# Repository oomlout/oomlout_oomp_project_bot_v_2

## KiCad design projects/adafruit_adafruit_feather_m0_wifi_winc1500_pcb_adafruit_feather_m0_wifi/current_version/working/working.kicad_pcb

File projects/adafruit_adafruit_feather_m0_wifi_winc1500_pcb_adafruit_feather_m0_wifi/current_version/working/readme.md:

# adafruit_feather_m0_wifi_winc1500_pcb
 
## summary 
* id: adafruit_adafruit_feather_m0_wifi_winc1500_pcb_adafruit_feather_m0_wifi
* user: adafruit
* name: adafruit_feather_m0_wifi_winc1500_pcb
* board: adafruit_feather_m0_wifi
* repo: https://github.com/adafruit/Adafruit-Feather-M0-WiFi-WINC1500-PCB

* src_file_repo_sch: 
* src_file_repo_sch_link: https://github.com/adafruit/Adafruit-Feather-M0-WiFi-WINC1500-PCB/tree/master/
* full details link: https://github.com/oomlout/oomlout_oomp_project_bot_v_2/tree/main/projects/adafruit_adafruit_feather_m0_wifi_winc1500_pcb_adafruit_feather_m0_wifi/current_version/working  

## schematic  
  
[schematic (pdf)](working_schematic.pdf) 

## pcb  

[board (pdf)](working.pdf)  

## working_bom
| Id | Designator | Footprint | Quantity | Designation | Supplier and ref |  | None | 
| --- | --- | --- | --- | --- | --- | --- | --- | 
| 1 | X1 | JSTPH2 | 1 | JSTPH |  |  | [''] | 
| 2 | R2,R11 | 0603-NO | 2 | 1K |  |  | [''] | 
| 3 | R10,R5 | 0603-NO | 2 | 1k |  |  | [''] | 
| 4 | R6 | 0603-NO | 1 | 100K |  |  | [''] | 
| 5 | U$32,U$31 | MOUNTINGHOLE_2.5_PLATED | 2 | MOUNTINGHOLE2.5 |  |  | [''] | 
| 6 | @HOLE1,@HOLE0 |  | 2 |  |  |  | [''] | 
| 7 | R3,R9,R1,R4 | 0603-NO | 4 | 100k |  |  | [''] | 
| 8 | NET0 | CHIPLED_0805_NOOUTLINE | 1 | YELLOW |  |  | [''] | 
| 9 | C2,C4 | 0603-NO | 2 | 22pF |  |  | [''] | 
| 10 | X3 | 4UCONN_20329_V2 | 1 | microUSB |  |  | [''] | 
| 11 | C14,C7,C1 | 0603-NO | 3 | 1uF |  |  | [''] | 
| 12 | U$7,U$12 | ADAFRUIT_3.5MM | 2 |  |  |  | [''] | 
| 13 | C8,C3,C6 | 0805-NO | 3 | 10ÂµF |  |  | [''] | 
| 14 | U$35,U$34 | FIDUCIAL_1MM | 2 | FIDUCIAL" |  |  | [''] | 
| 15 | U2 | SOT23-5 | 1 | AP2112K-3.3 |  |  | [''] | 
| 16 | JP1 | 1X16_ROUND | 1 |  |  |  | [''] | 
| 17 | WIFI0 | CHIPLED_0805_NOOUTLINE | 1 | GREEN |  |  | [''] | 
| 18 | C5 | 0805-NO | 1 | 10uF |  |  | [''] | 
| 19 | U3 | SOT23-5 | 1 | MCP73831T-2ACI/OT |  |  | [''] | 
| 20 | L0 | CHIPLED_0805_NOOUTLINE | 1 | RED |  |  | [''] | 
| 21 | X2 | XTAL3215 | 1 | 32.768 |  |  | [''] | 
| 22 | CHG0 | CHIPLED_0805_NOOUTLINE | 1 | ORANGE |  |  | [''] | 
| 23 | X4 | ATWINC1500_MR210PA | 1 | ATWINC1500_MR210PA |  |  | [''] | 
| 24 | R7 | 0603-NO | 1 | 2.2K |  |  | [''] | 
| 25 | U$4 | TQFN48_7MM | 1 | ATSAMD21G18_QFN |  |  | [''] | 
| 26 | D1 | SOD-123 | 1 | MBR120 |  |  | [''] | 
| 27 | JP3 | 1X12_ROUND | 1 |  |  |  | [''] | 
| 28 | SW1 | KMR2 | 1 | SPST_TACT-KMR2 |  |  | [''] | 
| 29 | R8 | 0603-NO | 1 | 4.7K |  |  | [''] | 
| 30 | TP1,TP2 | TESTPOINT_ROUND_1.5MM | 2 |  |  |  | [''] | 
| 31 | U$9 | FEATHERLOGO | 1 |  |  |  | [''] | 
| 32 | U$13 | PCBFEAT-REV-040 | 1 |  |  |  | [''] | 

## bom_schematic
| Ref | Qnty | Value | Cmp name | Footprint | Description | Vendor | DNP | 
| --- | --- | --- | --- | --- | --- | --- | --- | 
| C1, C7, C14 | 3 | 1uF | CAP_CERAMIC0603_NO | working:0603-NO |  |  |  | 
| C2, C4 | 2 | 22pF | CAP_CERAMIC0603_NO | working:0603-NO |  |  |  | 
| C3, C6, C8 | 3 | 10ÂµF | CAP_CERAMIC0805-NOOUTLINE | working:0805-NO |  |  |  | 
| C5 | 1 | 10uF | CAP_CERAMIC0805-NOOUTLINE | working:0805-NO |  |  |  | 
| CHG0 | 1 | ORANGE | LED0805_NOOUTLINE | working:CHIPLED_0805_NOOUTLINE |  |  |  | 
| D1 | 1 | MBR120 | DIODE-SCHOTTKYSOD-123 | working:SOD-123 |  |  |  | 
| JP1 | 1 | HEADER-1X16ROUND | HEADER-1X16ROUND | working:1X16_ROUND |  |  |  | 
| JP3 | 1 | HEADER-1X12 | HEADER-1X12 | working:1X12_ROUND |  |  |  | 
| L0 | 1 | RED | LED0805_NOOUTLINE | working:CHIPLED_0805_NOOUTLINE |  |  |  | 
| NET0 | 1 | YELLOW | LED0805_NOOUTLINE | working:CHIPLED_0805_NOOUTLINE |  |  |  | 
| R1, R3, R4, R9 | 4 | 100k | RESISTOR_0603_NOOUT | working:0603-NO |  |  |  | 
| R2, R11 | 2 | 1K | RESISTOR_0603_NOOUT | working:0603-NO |  |  |  | 
| R5, R10 | 2 | 1k | RESISTOR_0603_NOOUT | working:0603-NO |  |  |  | 
| R6 | 1 | 100K | RESISTOR_0603_NOOUT | working:0603-NO |  |  |  | 
| R7 | 1 | 2.2K | RESISTOR_0603_NOOUT | working:0603-NO |  |  |  | 
| R8 | 1 | 4.7K | RESISTOR_0603_NOOUT | working:0603-NO |  |  |  | 
| SW1 | 1 | SPST_TACT-KMR2 | SPST_TACT-KMR2 | working:KMR2 |  |  |  | 
| TP1, TP2 | 2 | TESTPOINTROUND1.5MM | TESTPOINTROUND1.5MM | working:TESTPOINT_ROUND_1.5MM |  |  |  | 
| U2 | 1 | AP2112K-3.3 | VREG_SOT23-5 | working:SOT23-5 |  |  |  | 
| U3 | 1 | MCP73831T-2ACI/OT | MCP73831/2 | working:SOT23-5 |  |  |  | 
| U$4 | 1 | ATSAMD21J_QFN | ATSAMD21J_QFN | working:TQFN48_7MM |  |  |  | 
| U$31, U$32 | 2 | MOUNTINGHOLE2.5 | MOUNTINGHOLE2.5 | working:MOUNTINGHOLE_2.5_PLATED |  |  |  | 
| U$34, U$35 | 2 | FIDUCIAL"" | FIDUCIAL{dblquote}{dblquote} | working:FIDUCIAL_1MM |  |  |  | 
| WIFI0 | 1 | GREEN | LED0805_NOOUTLINE | working:CHIPLED_0805_NOOUTLINE |  |  |  | 
| X1 | 1 | JSTPH | CON_JST_PH_2PIN | working:JSTPH2 |  |  |  | 
| X2 | 1 | 32.768 | XTAL-3.2X1.5 | working:XTAL3215 |  |  |  | 
| X3 | 1 | microUSB | USB_MICRO_20329_V2 | working:4UCONN_20329_V2 |  |  |  | 
| X4 | 1 | ATWINC1500_MR210PA | ATWINC1500_MR210PA | working:ATWINC1500_MR210PA |  |  |  | 

## mounting_holes
| x | y | package | value | ref | size | 
| --- | --- | --- | --- | --- | --- | 
| 0.0 | 17.78 | MOUNTINGHOLE_2.5_PLATED | MOUNTINGHOLE2.5 | U$31 | m3 | 
| 0.0 | 0.0 | MOUNTINGHOLE_2.5_PLATED | MOUNTINGHOLE2.5 | U$32 | m3 |

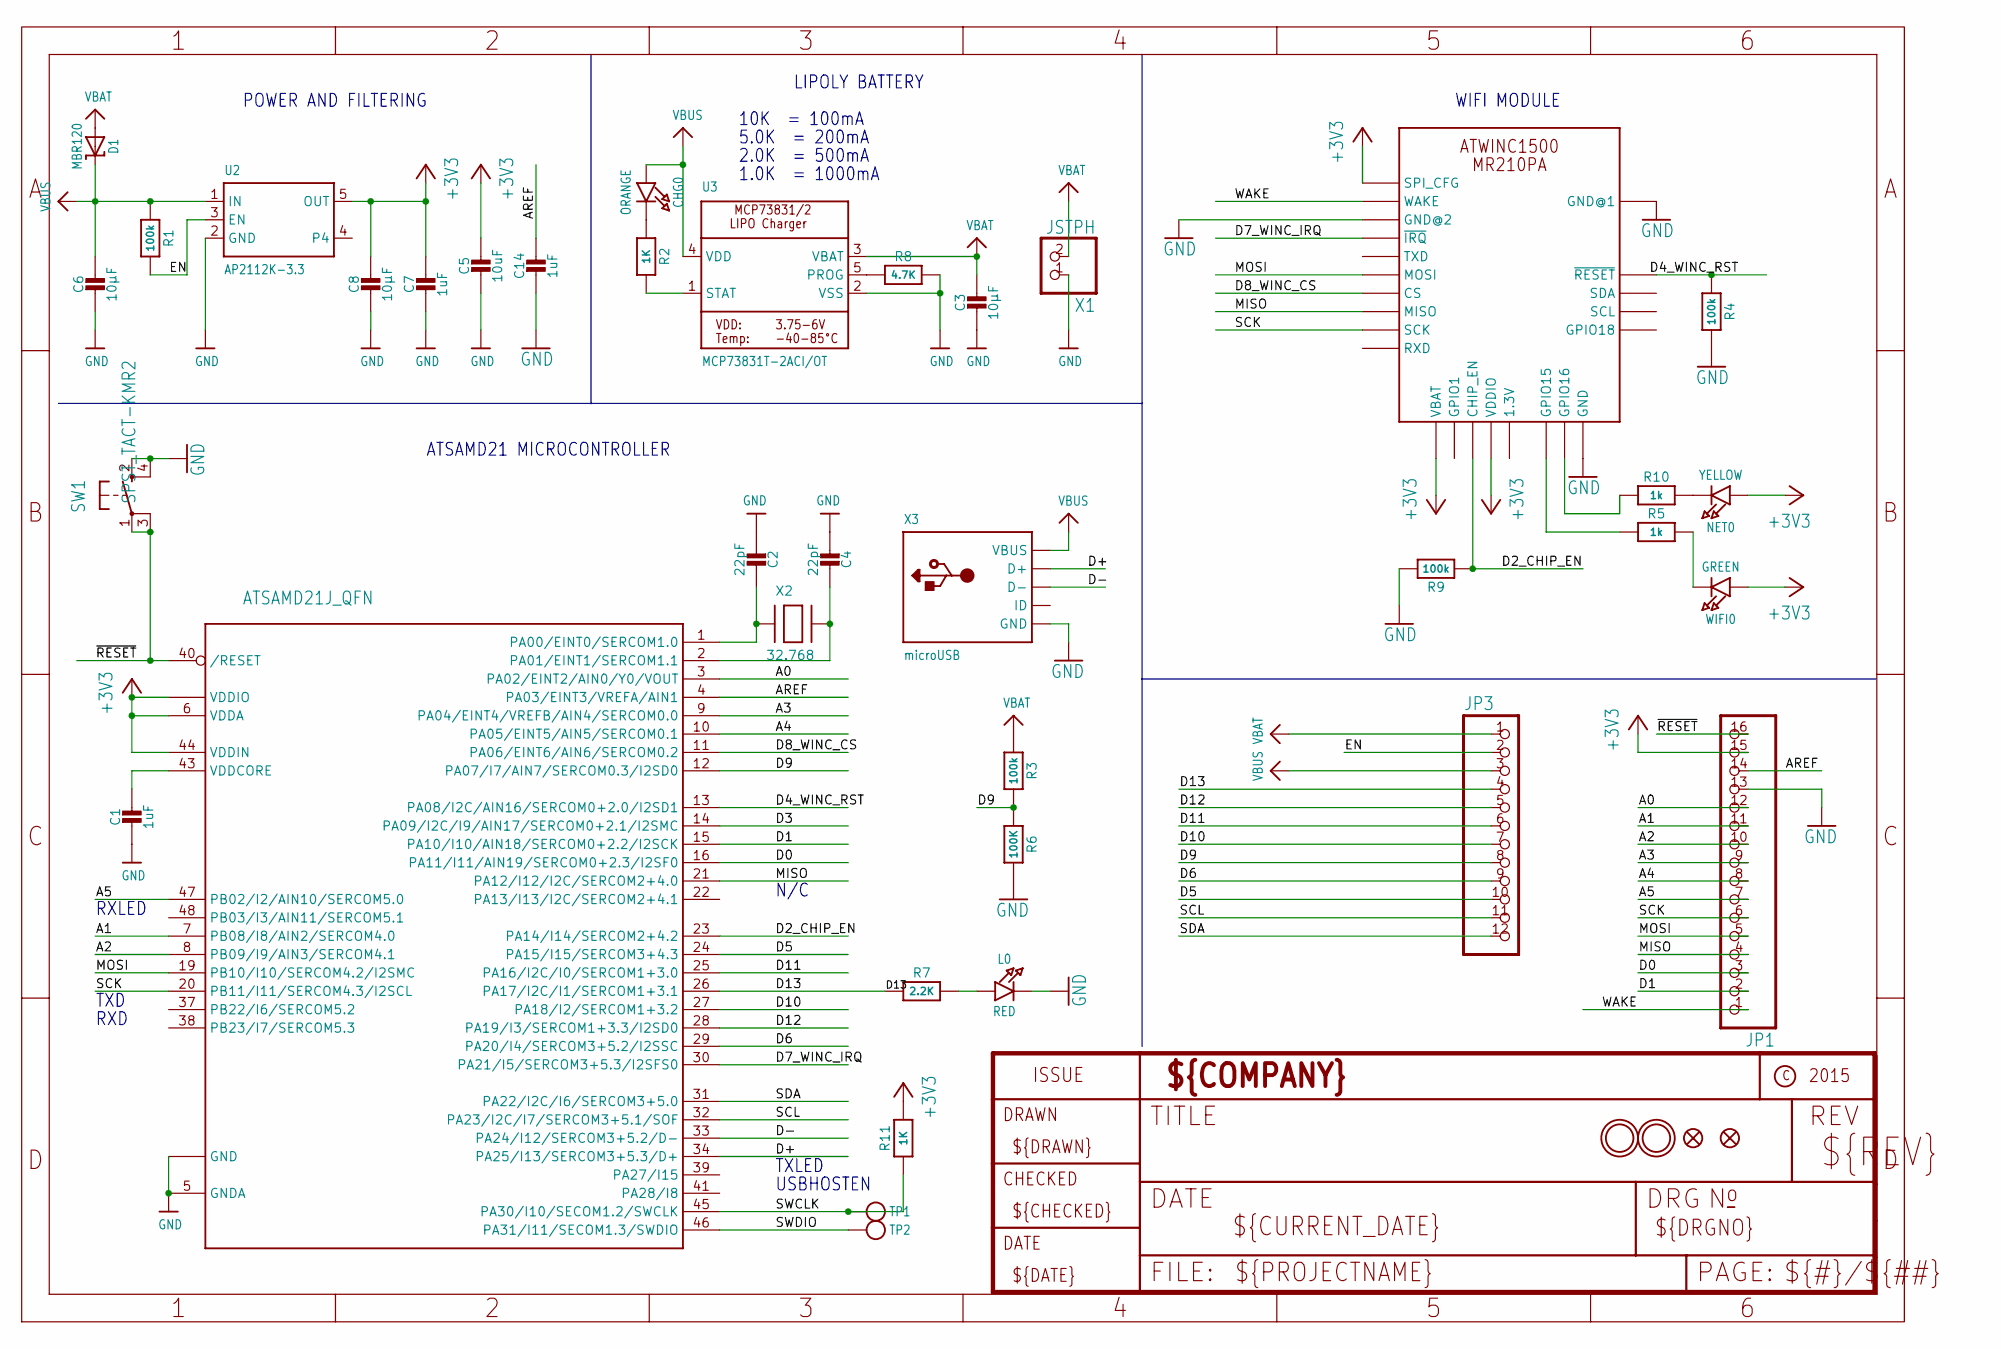
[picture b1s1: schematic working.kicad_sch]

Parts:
C1, C7, C14: 1uF; 0603-NO
C2, C4: 22pF; 0603-NO
C3, C6, C8: 10µF; 0805-NO
C5: 10uF; 0805-NO
CHG0: ORANGE; CHIPLED_0805_NOOUTLINE
D1: MBR120; SOD-123
JP1: HEADER-1X16ROUND; 1X16_ROUND
JP3: HEADER-1X12; 1X12_ROUND
L0: RED; CHIPLED_0805_NOOUTLINE
NET0: YELLOW; CHIPLED_0805_NOOUTLINE
R1, R3, R4, R9: 100k; 0603-NO
R2, R11: 1K; 0603-NO
R5, R10: 1k; 0603-NO
R6: 100K; 0603-NO
R7: 2.2K; 0603-NO
R8: 4.7K; 0603-NO
SW1: SPST_TACT-KMR2; KMR2
TP1, TP2: TESTPOINTROUND1.5MM; TESTPOINT_ROUND_1.5MM
U2: AP2112K-3.3; SOT23-5
U3: MCP73831T-2ACI/OT; SOT23-5
U$4: ATSAMD21J_QFN; TQFN48_7MM
U$31, U$32: MOUNTINGHOLE2.5; MOUNTINGHOLE_2.5_PLATED
U$34, U$35: FIDUCIAL""; FIDUCIAL_1MM
WIFI0: GREEN; CHIPLED_0805_NOOUTLINE
X1: JSTPH; JSTPH2
X2: 32.768; XTAL3215
X3: microUSB; 4UCONN_20329_V2
X4: ATWINC1500_MR210PA

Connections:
+3V3: C5.1, C7.1, C8.1, JP1.15, NET0.A, R11.2, U2.5 (OUT), U$4.6 (VDDA), U$4.17 (VDDIO), U$4.36 (VDDIO), U$4.44 (VDDIN), WIFI0.A, X4.J10 (SPI_CFG), X4.J20 (VBAT), X4.J23 (VDDIO)
A0: JP1.12, U$4.3 (PA02/EINT2/AIN0/Y0/VOUT)
A1: JP1.11, U$4.7 (PB08/I8/AIN2/SERCOM4.0)
A2: JP1.10, U$4.8 (PB09/I9/AIN3/SERCOM4.1)
A3: JP1.9, U$4.9 (PA04/EINT4/VREFB/AIN4/SERCOM0.0)
A4: JP1.8, U$4.10 (PA05/EINT5/AIN5/SERCOM0.1)
A5: JP1.7, U$4.47 (PB02/I2/AIN10/SERCOM5.0)
AREF: C14.1, JP1.14, U$4.4 (PA03/EINT3/VREFA/AIN1)
D0: JP1.3, U$4.16 (PA11/I11/AIN19/SERCOM0+2.3/I2SF0)
D1: JP1.2, U$4.15 (PA10/I10/AIN18/SERCOM0+2.2/I2SCK)
D2_CHIP_EN: R9.1, U$4.23 (PA14/I14/SERCOM2+4.2), X4.J22 (CHIP_EN)
D3: U$4.14 (PA09/I2C/I9/AIN17/SERCOM0+2.1/I2SMC)
D4_WINC_RST: R4.1, U$4.13 (PA08/I2C/AIN16/SERCOM0+2.0/I2SD1), X4.J4 (~RESET)
D5: JP3.10, U$4.24 (PA15/I15/SERCOM3+4.3)
D6: JP3.9, U$4.29 (PA20/I4/SERCOM3+5.2/I2SSC)
D7_WINC_IRQ: U$4.30 (PA21/I5/SERCOM3+5.3/I2SFS0), X4.J13 (~IRQ)
D8_WINC_CS: U$4.11 (PA06/EINT6/AIN6/SERCOM0.2), X4.J16 (CS)
D9: JP3.8, R3.2, R6.1, U$4.12 (PA07/I7/AIN7/SERCOM0.3/I2SD0)
D10: JP3.7, U$4.27 (PA18/I2/SERCOM1+3.2)
D11: JP3.6, U$4.25 (PA16/I2C/I0/SERCOM1+3.0)
D12: JP3.5, U$4.28 (PA19/I3/SERCOM1+3.3/I2SD0)
D13: JP3.4, R7.1, U$4.26 (PA17/I2C/I1/SERCOM1+3.1)
D+: U$4.34 (PA25/I13/SERCOM3+5.3/D+), X3.D+
D-: U$4.33 (PA24/I12/SERCOM3+5.2/D-), X3.D-
EN: JP3.2, R1.2, U2.3 (EN)
GND: C1.2, C2.2, C3.2, C4.2, C5.2, C6.2, C7.2, C8.2, C14.2, JP1.13, L0.C, R4.2, R6.2, R8.2, R9.2, SW1.2 (S), SW1.4 (S1), U2.2 (GND), U3.2 (VSS), U$4.5 (GNDA), U$4.18 (GND), U$4.35 (GND), U$4.42 (GND), U$4.THERMAL (GND), X1.1, X3.BASE@1 (GND), X3.BASE@2 (GND), X3.GND, X3.SPRT@1 (GND), X3.SPRT@2 (GND), X3.SPRT@3 (GND), X3.SPRT@4 (GND), X4.J9 (GND@1), X4.J12 (GND@2), X4.J28 (GND), X4.MTGND (GND)
MISO: JP1.4, U$4.21 (PA12/I12/I2C/SERCOM2+4.0), X4.J17 (MISO)
MOSI: JP1.5, U$4.19 (PB10/I10/SERCOM4.2/I2SMC), X4.J15 (MOSI)
unnamed: CHG0.C, R2.1
unnamed: L0.A, R7.2
unnamed: R2.2, U3.1 (STAT)
unnamed: R8.1, U3.5 (PROG)
unnamed: C2.1, U$4.1 (PA00/EINT0/SERCOM1.0), X2.P$1
unnamed: R5.1, X4.J26 (GPIO15)
unnamed: C4.1, U$4.2 (PA01/EINT1/SERCOM1.1), X2.P$2
unnamed: R10.1, X4.J27 (GPIO16)
unnamed: R5.2, WIFI0.C
unnamed: NET0.C, R10.2
SCK: JP1.6, U$4.20 (PB11/I11/SERCOM4.3/I2SCL), X4.J18 (SCK)
SCL: JP3.11, U$4.32 (PA23/I2C/I7/SERCOM3+5.1/SOF)
SDA: JP3.12, U$4.31 (PA22/I2C/I6/SERCOM3+5.0)
SWCLK: R11.1, TP1.P$1, U$4.45 (PA30/I10/SECOM1.2/SWCLK)
SWDIO: TP2.P$1, U$4.46 (PA31/I11/SECOM1.3/SWDIO)
VBAT: C3.1, D1.A, JP3.1, R3.1, U3.3 (VBAT), X1.2
VBUS: C6.1, CHG0.A, D1.C, JP3.3, R1.1, U2.1 (IN), U3.4 (VDD), X3.VBUS
VDDCORE: C1.1, U$4.43 (VDDCORE)
WAKE: JP1.1, X4.J11 (WAKE)
~RESET: JP1.16, SW1.1, SW1.3 (P1), U$4.40 (/RESET)

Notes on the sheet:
N/C
LIPOLY BATTERY
1.0K = 1000mA
5.0K = 200mA
WIFI MODULE
10K = 100mA
ATSAMD21 MICROCONTROLLER
POWER AND FILTERING
TXLED
2.0K = 500mA
USBHOSTEN
RXD
RXLED
TXD

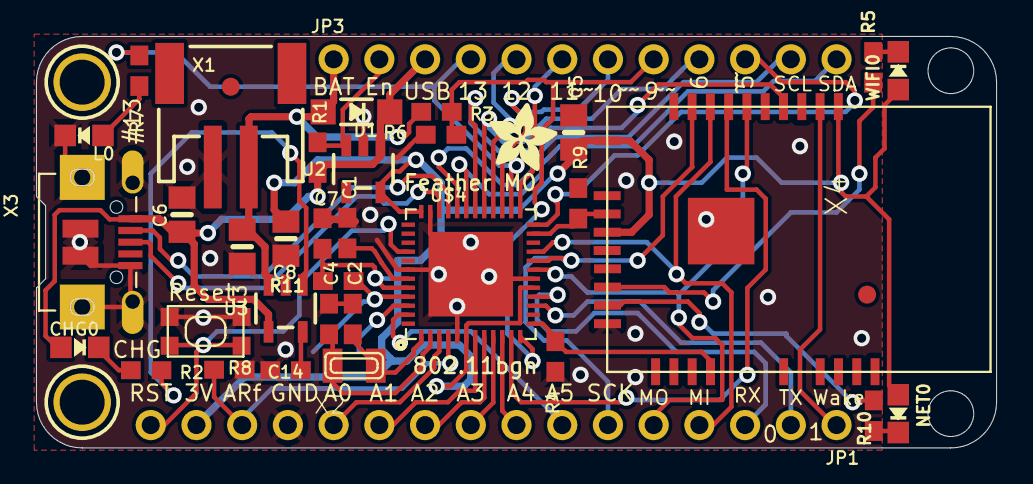
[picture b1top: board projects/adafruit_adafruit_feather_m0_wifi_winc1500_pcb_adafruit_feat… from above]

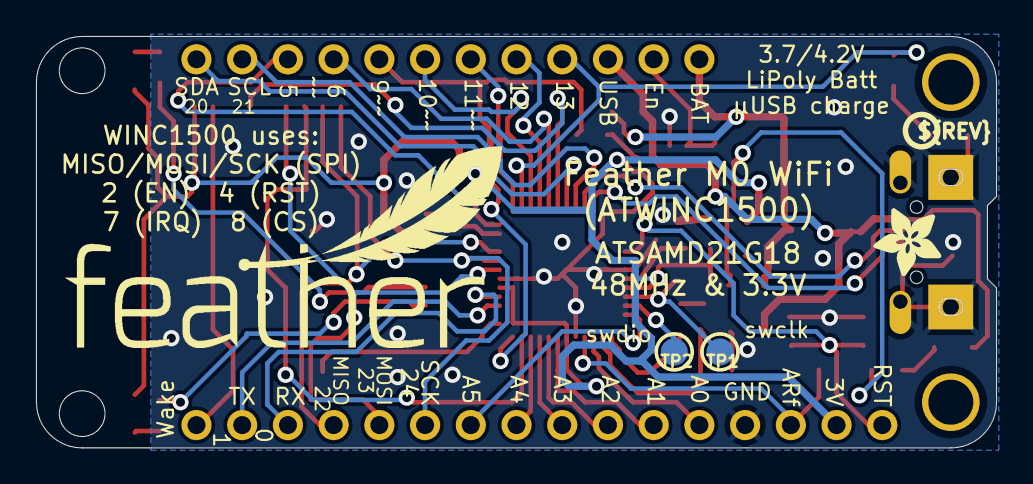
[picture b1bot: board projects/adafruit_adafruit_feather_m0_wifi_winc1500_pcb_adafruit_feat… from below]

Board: 2 copper layers, 53.3 x 22.9 mm, 47 parts (5 on the bottom side), 47 nets.

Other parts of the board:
@HOLE0, @HOLE1: (no value)
U$7, U$12: ADAFRUIT_3.5MM
U$9: FEATHERLOGO
U$13: PCBFEAT-REV-040

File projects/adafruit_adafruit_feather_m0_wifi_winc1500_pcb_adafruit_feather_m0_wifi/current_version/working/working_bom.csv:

"Id";"Designator";"Footprint";"Quantity";"Designation";"Supplier and ref";
1;"X1";"JSTPH2";1;"JSTPH";;;
2;"R2,R11";"0603-NO";2;"1K";;;
3;"R10,R5";"0603-NO";2;"1k";;;
4;"R6";"0603-NO";1;"100K";;;
5;"U$32,U$31";"MOUNTINGHOLE_2.5_PLATED";2;"MOUNTINGHOLE2.5";;;
6;"@HOLE1,@HOLE0";"";2;"";;;
7;"R3,R9,R1,R4";"0603-NO";4;"100k";;;
8;"NET0";"CHIPLED_0805_NOOUTLINE";1;"YELLOW";;;
9;"C2,C4";"0603-NO";2;"22pF";;;
10;"X3";"4UCONN_20329_V2";1;"microUSB";;;
11;"C14,C7,C1";"0603-NO";3;"1uF";;;
12;"U$7,U$12";"ADAFRUIT_3.5MM";2;"";;;
13;"C8,C3,C6";"0805-NO";3;"10µF";;;
14;"U$35,U$34";"FIDUCIAL_1MM";2;"FIDUCIAL""";;;
15;"U2";"SOT23-5";1;"AP2112K-3.3";;;
16;"JP1";"1X16_ROUND";1;"";;;
17;"WIFI0";"CHIPLED_0805_NOOUTLINE";1;"GREEN";;;
18;"C5";"0805-NO";1;"10uF";;;
19;"U3";"SOT23-5";1;"MCP73831T-2ACI/OT";;;
20;"L0";"CHIPLED_0805_NOOUTLINE";1;"RED";;;
21;"X2";"XTAL3215";1;"32.768";;;
22;"CHG0";"CHIPLED_0805_NOOUTLINE";1;"ORANGE";;;
23;"X4";"ATWINC1500_MR210PA";1;"ATWINC1500_MR210PA";;;
24;"R7";"0603-NO";1;"2.2K";;;
25;"U$4";"TQFN48_7MM";1;"ATSAMD21G18_QFN";;;
26;"D1";"SOD-123";1;"MBR120";;;
27;"JP3";"1X12_ROUND";1;"";;;
28;"SW1";"KMR2";1;"SPST_TACT-KMR2";;;
29;"R8";"0603-NO";1;"4.7K";;;
30;"TP1,TP2";"TESTPOINT_ROUND_1.5MM";2;"";;;
31;"U$9";"FEATHERLOGO";1;"";;;
32;"U$13";"PCBFEAT-REV-040";1;"";;;

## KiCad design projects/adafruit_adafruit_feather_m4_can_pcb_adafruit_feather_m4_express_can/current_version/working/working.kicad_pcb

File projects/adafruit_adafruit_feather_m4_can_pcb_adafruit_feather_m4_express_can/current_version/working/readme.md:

# adafruit_feather_m4_can_pcb
 
## summary 
* id: adafruit_adafruit_feather_m4_can_pcb_adafruit_feather_m4_express_can
* user: adafruit
* name: adafruit_feather_m4_can_pcb
* board: adafruit_feather_m4_express_can
* repo: https://github.com/adafruit/Adafruit-Feather-M4-CAN-PCB

* src_file_repo_sch: 
* src_file_repo_sch_link: https://github.com/adafruit/Adafruit-Feather-M4-CAN-PCB/tree/main/
* full details link: https://github.com/oomlout/oomlout_oomp_project_bot_v_2/tree/main/projects/adafruit_adafruit_feather_m4_can_pcb_adafruit_feather_m4_express_can/current_version/working  

## schematic  
  
[schematic (pdf)](working_schematic.pdf) 

## pcb  

[board (pdf)](working.pdf)  

## working_bom
| Id | Designator | Footprint | Quantity | Designation | Supplier and ref |  | None | 
| --- | --- | --- | --- | --- | --- | --- | --- | 
| 1 | C11,C12,C15,C14,C10,C7 | 0603-NO | 6 | 1uF |  |  | [''] | 
| 2 | X6 | USB_C_CUSB31-CFM2AX-01-X | 1 | USB Type C |  |  | [''] | 
| 3 | C13,C17,C5 | 0805-NO | 3 | 10uF |  |  | [''] | 
| 4 | R12,R13,R8 | 0603-NO | 3 | 5.1K |  |  | [''] | 
| 5 | X1 | JSTPH2_BATT | 1 | JSTPH |  |  | [''] | 
| 6 | U$35,U$34 | FIDUCIAL_1MM | 2 | FIDUCIAL_1MM |  |  | [''] | 
| 7 | U3 | SOT23-5 | 1 | MCP73831T-2ACI/OT |  |  | [''] | 
| 8 | R9 | RESPACK_4X0603_NO | 1 | 100K |  |  | [''] | 
| 9 | C6,C8,C3 | 0805-NO | 3 | 10ÂµF |  |  | [''] | 
| 10 | R2,R7,R5,R4,R6,R3 | 0603-NO | 6 | 10K |  |  | [''] | 
| 11 | X2 | XTAL3215 | 1 | 32.768 |  |  | [''] | 
| 12 | U$32,U$31 | MOUNTINGHOLE_2.5_PLATED | 2 | MOUNTINGHOLE2.5 |  |  | [''] | 
| 13 | SW1 | BTN_KMR2_4.6X2.8 | 1 | KMR2 |  |  | [''] | 
| 14 | JP1 | 1X16_ROUND | 1 |  |  |  | [''] | 
| 15 | U$1 | ADAFRUIT_2.5MM | 1 |  |  |  | [''] | 
| 16 | @HOLE0,@HOLE1 |  | 2 |  |  |  | [''] | 
| 17 | CHG0 | CHIPLED_0603_NOOUTLINE | 1 | ORANGE |  |  | [''] | 
| 18 | C2,C4 | 0603-NO | 2 | 22pF |  |  | [''] | 
| 19 | SJ2,SJ1 | SOLDERJUMPER_CLOSEDWIRE | 2 |  |  |  | [''] | 
| 20 | U$14 | PQFN64-1 | 1 | ATSAMD51J |  |  | [''] | 
| 21 | JP3 | 1X12_ROUND | 1 |  |  |  | [''] | 
| 22 | C16 | _0805MP | 1 | 10uF |  |  | [''] | 
| 23 | U1 | USON8 | 1 | 2MB Flash |  |  | [''] | 
| 24 | L0 | CHIPLED_0603_NOOUTLINE | 1 | RED |  |  | [''] | 
| 25 | R11,R10 | 0805-NO | 2 | 60 ohm |  |  | [''] | 
| 26 | IC3 | SOT23-6 | 1 | AP3602 |  |  | [''] | 
| 27 | Q3 | SOT23-R | 1 | DMG341 |  |  | [''] | 
| 28 | LED1 | LED3535 | 1 | WS2812B3535 |  |  | [''] | 
| 29 | X4 | TERMBLOCK_1X3-3.5MM | 1 | 3.5mm |  |  | [''] | 
| 30 | U2 | SOT23-5@1 | 1 | AP2112-3.3 |  |  | [''] | 
| 31 | IC1 | SOIC8_150MIL | 1 | TCAN1051HGV |  |  | [''] | 
| 32 | D4 | SOD-123 | 1 | MBR540 |  |  | [''] | 
| 33 | L2 | INDUCTOR_1007 | 1 | 10uH |  |  | [''] | 
| 34 | C18 | 0805_10MGAP | 1 | 1uF |  |  | [''] | 
| 35 | D-1,D+1 | B1,27 | 2 | TPB1,27 |  |  | [''] | 
| 36 | U$12 | ADAFRUIT_3.5MM | 1 |  |  |  | [''] | 
| 37 | U$9 | FEATHERLOGO | 1 |  |  |  | [''] | 
| 38 | TP2,TP1 | TESTPOINT_ROUND_1.5MM | 2 |  |  |  | [''] | 
| 39 | U$13 | PCBFEAT-REV-040 | 1 |  |  |  | [''] | 

## bom_schematic
| Ref | Qnty | Value | Cmp name | Footprint | Description | Vendor | DNP | 
| --- | --- | --- | --- | --- | --- | --- | --- | 
| C2, C4 | 2 | 22pF | CAP_CERAMIC0603_NO | working:0603-NO |  |  |  | 
| C3, C6, C8 | 3 | 10ÂµF | CAP_CERAMIC0805-NOOUTLINE | working:0805-NO |  |  |  | 
| C5, C13, C17 | 3 | 10uF | CAP_CERAMIC0805-NOOUTLINE | working:0805-NO |  |  |  | 
| C7, C10, C11, C12, C14, C15 | 6 | 1uF | CAP_CERAMIC0603_NO | working:0603-NO |  |  |  | 
| C16 | 1 | 10uF | CAP_CERAMIC_0805MP | working:_0805MP |  |  |  | 
| C18 | 1 | 1uF | CAP_CERAMIC0805_10MGAP | working:0805_10MGAP |  |  |  | 
| CHG0 | 1 | ORANGE | LED0603_NOOUTLINE | working:CHIPLED_0603_NOOUTLINE |  |  |  | 
| D4 | 1 | MBR540 | DIODE-SCHOTTKYSOD-123 | working:SOD-123 |  |  |  | 
| D+1 | 1 | TPB1,27 | TPB1,27 | working:B1,27 |  |  |  | 
| D-1 | 1 | TPB1,27 | TPB1,27 | working:B1,27 |  |  |  | 
| IC1 | 1 | TCAN1051HGV | CAN_TRANSCIEVER_TCAN1051V | working:SOIC8_150MIL |  |  |  | 
| IC3 | 1 | AP3602 | AP3602 | working:SOT23-6 |  |  |  | 
| JP1 | 1 | HEADER-1X16ROUND | HEADER-1X16ROUND | working:1X16_ROUND |  |  |  | 
| JP3 | 1 | HEADER-1X12 | HEADER-1X12 | working:1X12_ROUND |  |  |  | 
| L0 | 1 | RED | LED0603_NOOUTLINE | working:CHIPLED_0603_NOOUTLINE |  |  |  | 
| L2 | 1 | 10uH | INDUCTOR | working:INDUCTOR_1007 |  |  |  | 
| LED1 | 1 | WS2812B3535 | WS2812B3535 | working:LED3535 |  |  |  | 
| Q3 | 1 | DMG341 | MOSFET-P | working:SOT23-R |  |  |  | 
| R2, R3, R4, R5, R6, R7 | 6 | 10K | RESISTOR_0603_NOOUT | working:0603-NO |  |  |  | 
| R8, R12, R13 | 3 | 5.1K | RESISTOR_0603_NOOUT | working:0603-NO |  |  |  | 
| R9 | 1 | 100K | RESISTOR_4PACK_NO | working:RESPACK_4X0603_NO |  |  |  | 
| R10, R11 | 2 | 60 ohm | RESISTOR0805_NOOUTLINE | working:0805-NO |  |  |  | 
| SJ1 | 1 | SOLDERJUMPERCLOSED | SOLDERJUMPERCLOSED | working:SOLDERJUMPER_CLOSEDWIRE |  |  |  | 
| SJ2 | 1 | SOLDERJUMPER_CLOSED | SOLDERJUMPER_CLOSED | working:SOLDERJUMPER_CLOSEDWIRE |  |  |  | 
| SW1 | 1 | KMR2 | SWITCH_TACT_SMT4.6X2.8 | working:BTN_KMR2_4.6X2.8 |  |  |  | 
| TP1, TP2 | 2 | TESTPOINTROUND1.5MM | TESTPOINTROUND1.5MM | working:TESTPOINT_ROUND_1.5MM |  |  |  | 
| U1 | 1 | 2MB Flash | SPIFLASH_8PINUX | working:USON8 |  |  |  | 
| U2 | 1 | AP2112-3.3 | VREG_SOT23-5 | working:SOT23-5@1 |  |  |  | 
| U3 | 1 | MCP73831T-2ACI/OT | MCP73831/2 | working:SOT23-5 |  |  |  | 
| U$14 | 1 | ATSAMD51J | ATSAMD51J | working:PQFN64-1 |  |  |  | 
| U$31, U$32 | 2 | MOUNTINGHOLE2.5 | MOUNTINGHOLE2.5 | working:MOUNTINGHOLE_2.5_PLATED |  |  |  | 
| U$34, U$35 | 2 | FIDUCIAL_1MM | FIDUCIAL_1MM | working:FIDUCIAL_1MM |  |  |  | 
| X1 | 1 | JSTPH | CON_JST_PH_2PIN_BATT | working:JSTPH2_BATT |  |  |  | 
| X2 | 1 | 32.768 | XTAL-3.2X1.5 | working:XTAL3215 |  |  |  | 
| X4 | 1 | 3.5mm | TERMBLOCK_1X3 | working:TERMBLOCK_1X3-3.5MM |  |  |  | 
| X6 | 1 | USB Type C | USB_C | working:USB_C_CUSB31-CFM2AX-01-X |  |  |  | 

## mounting_holes
| x | y | package | value | ref | size | 
| --- | --- | --- | --- | --- | --- | 
| 0.0 | 17.78 | MOUNTINGHOLE_2.5_PLATED | MOUNTINGHOLE2.5 | U$31 | m3 | 
| 0.0 | 0.0 | MOUNTINGHOLE_2.5_PLATED | MOUNTINGHOLE2.5 | U$32 | m3 |

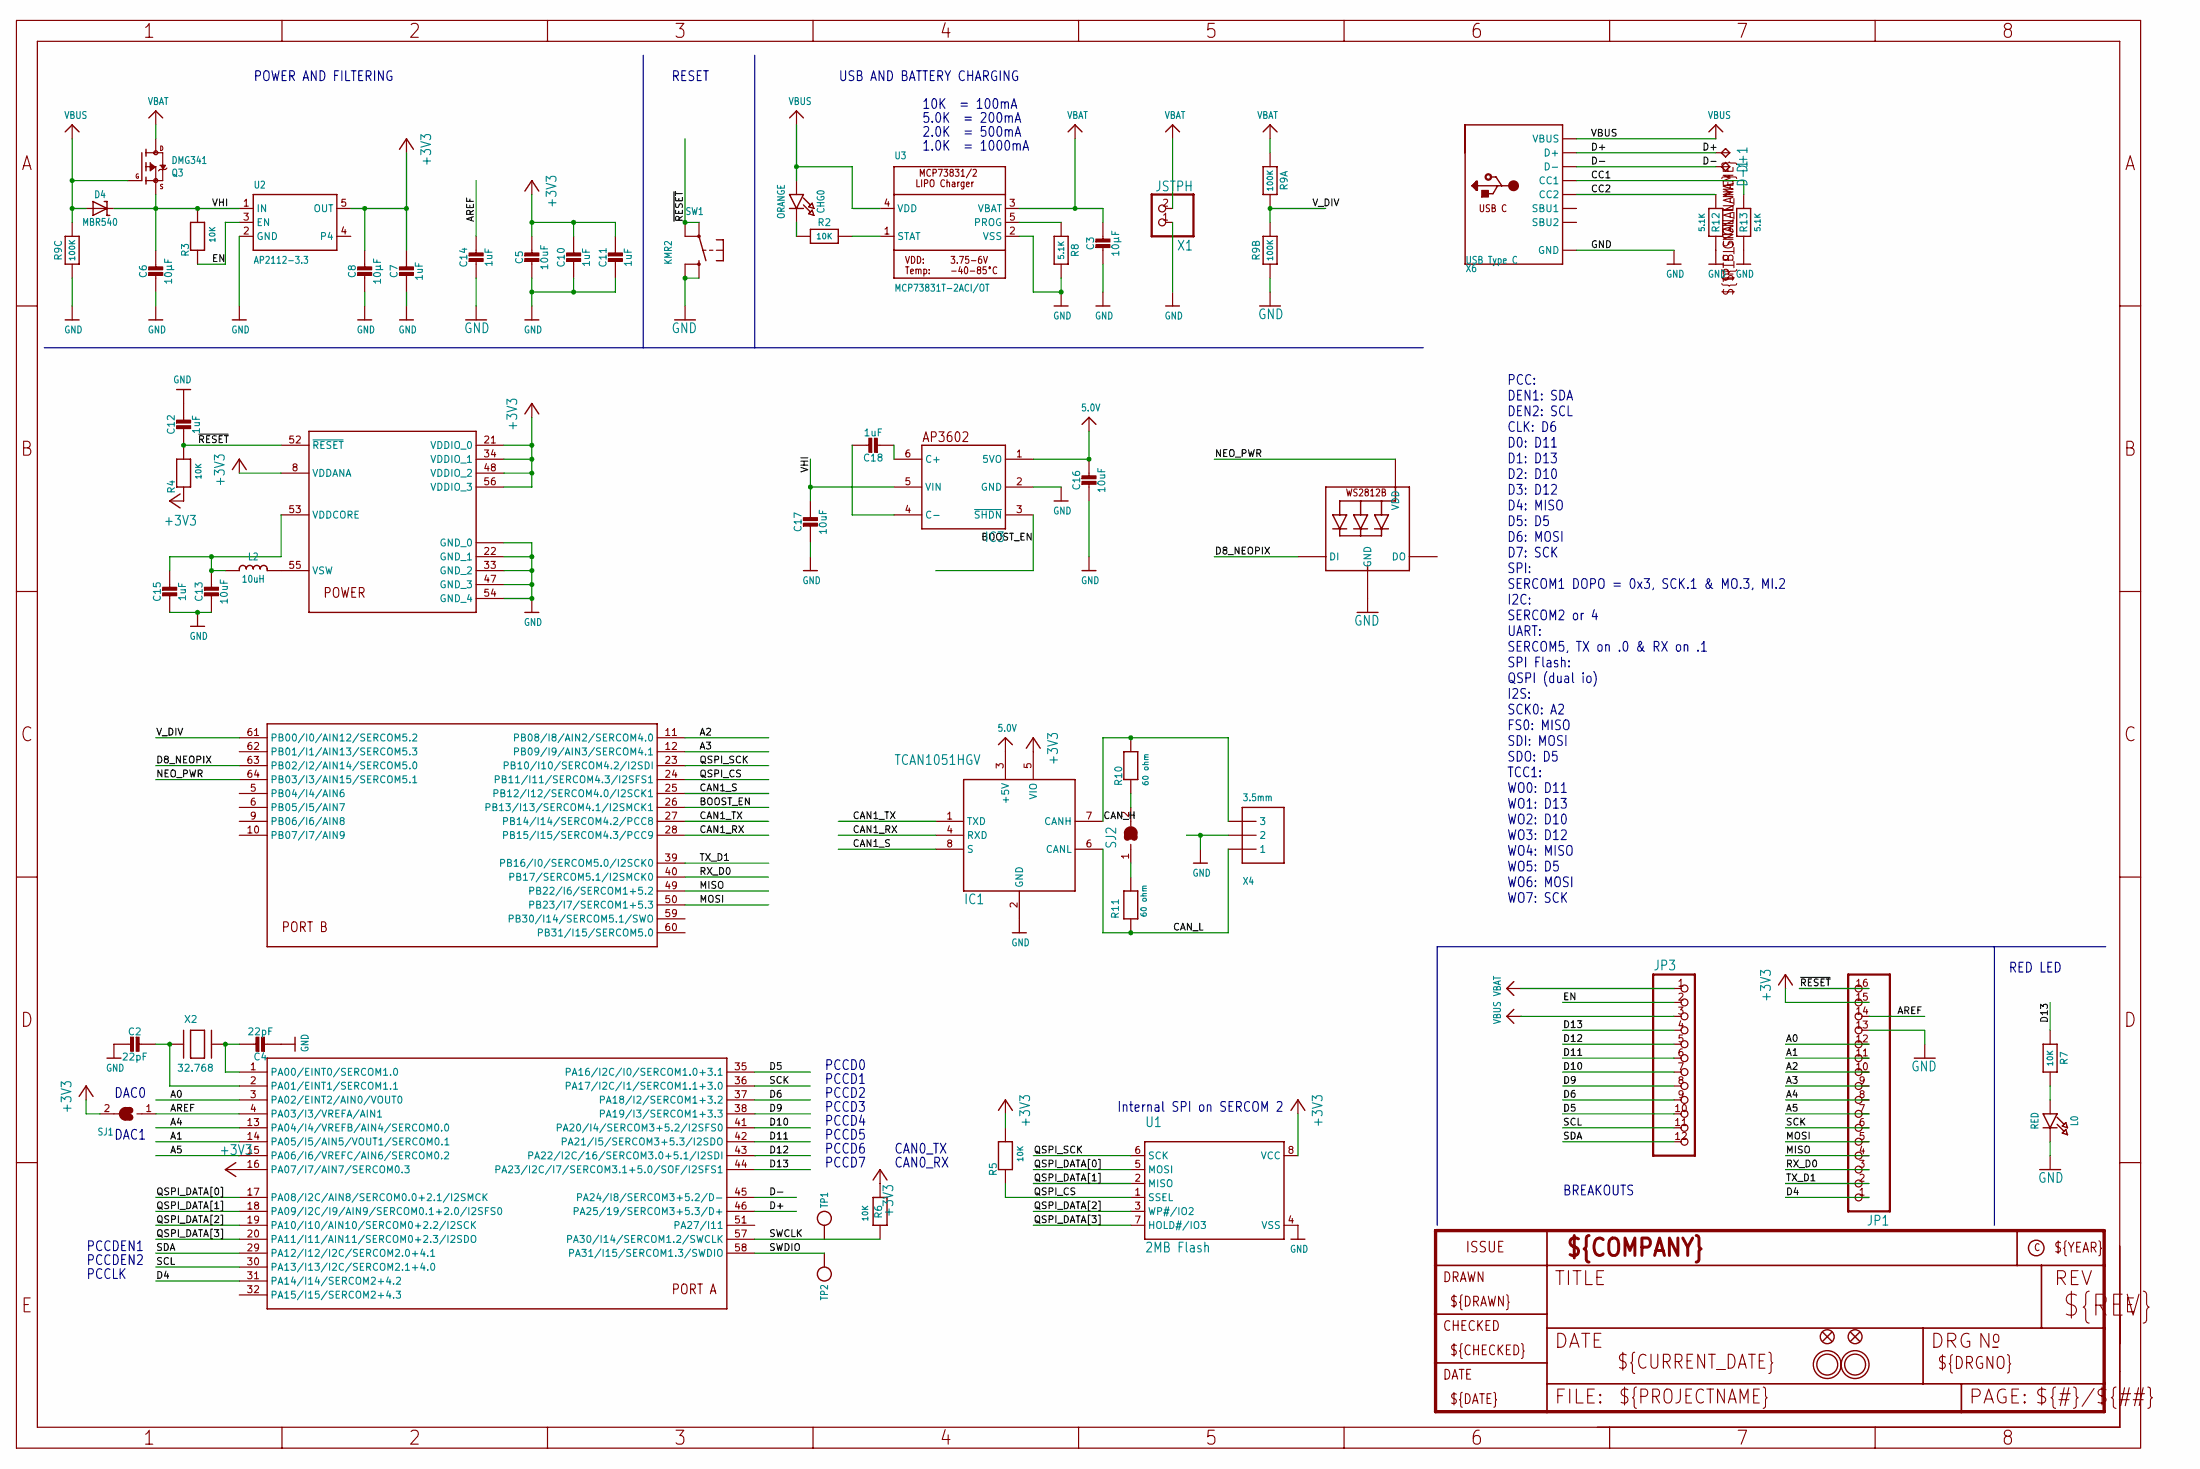
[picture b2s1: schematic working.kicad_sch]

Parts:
C2, C4: 22pF; 0603-NO
C3, C6, C8: 10µF; 0805-NO
C5, C13, C17: 10uF; 0805-NO
C7, C10, C11, C12, C14, C15: 1uF; 0603-NO
C16: 10uF; _0805MP
C18: 1uF; 0805_10MGAP
CHG0: ORANGE; CHIPLED_0603_NOOUTLINE
D4: MBR540; SOD-123
D+1: TPB1,27; B1,27
D-1: TPB1,27; B1,27
IC1: TCAN1051HGV; SOIC8_150MIL
IC3: AP3602; SOT23-6
JP1: HEADER-1X16ROUND; 1X16_ROUND
JP3: HEADER-1X12; 1X12_ROUND
L0: RED; CHIPLED_0603_NOOUTLINE
L2: 10uH; INDUCTOR_1007
LED1: WS2812B3535; LED3535
Q3: DMG341; SOT23-R
R2, R3, R4, R5, R6, R7: 10K; 0603-NO
R8, R12, R13: 5.1K; 0603-NO
R9: 100K; RESPACK_4X0603_NO
R10, R11: 60 ohm; 0805-NO
SJ1: SOLDERJUMPERCLOSED; SOLDERJUMPER_CLOSEDWIRE
SJ2: SOLDERJUMPER_CLOSED; SOLDERJUMPER_CLOSEDWIRE
SW1: KMR2; BTN_KMR2_4.6X2.8
TP1, TP2: TESTPOINTROUND1.5MM; TESTPOINT_ROUND_1.5MM
U1: 2MB Flash; USON8
U2: AP2112-3.3; SOT23-5@1
U3: MCP73831T-2ACI/OT; SOT23-5
U$14: ATSAMD51J; PQFN64-1
U$31, U$32: MOUNTINGHOLE2.5; MOUNTINGHOLE_2.5_PLATED
U$34, U$35: FIDUCIAL_1MM
X1: JSTPH; JSTPH2_BATT
X2: 32.768; XTAL3215
X4: 3.5mm; TERMBLOCK_1X3-3.5MM
X6: USB Type C; USB_C_CUSB31-CFM2AX-01-X

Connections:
5.0V: C16.1, IC1.3 (+5V), IC3.1 (5VO)
+3V3: C5.1, C7.1, C8.1, C10.1, C11.1, IC1.5 (VIO), JP1.15, R4.1, R5.2, R6.1, SJ1.2, U1.8 (VCC), U2.5 (OUT), U$14.8 (VDDANA), U$14.16 (PA07/I7/AIN7/SERCOM0.3), U$14.21 (VDDIO_0), U$14.34 (VDDIO_1), U$14.48 (VDDIO_2), U$14.56 (VDDIO_3)
A0: JP1.12, U$14.3 (PA02/EINT2/AIN0/VOUT0)
A1: JP1.11, U$14.14 (PA05/I5/AIN5/VOUT1/SERCOM0.1)
A2: JP1.10, U$14.11 (PB08/I8/AIN2/SERCOM4.0)
A3: JP1.9, U$14.12 (PB09/I9/AIN3/SERCOM4.1)
A4: JP1.8, U$14.13 (PA04/I4/VREFB/AIN4/SERCOM0.0)
A5: JP1.7, U$14.15 (PA06/I6/VREFC/AIN6/SERCOM0.2)
AREF: C14.1, JP1.14, SJ1.1, U$14.4 (PA03/I3/VREFA/AIN1)
BOOST_EN: IC3.3 (~SHDN), U$14.26 (PB13/I13/SERCOM4.1/I2SMCK1)
CAN1_RX: IC1.4 (RXD), U$14.28 (PB15/I15/SERCOM4.3/PCC9)
CAN1_S: IC1.8 (S), U$14.25 (PB12/I12/SERCOM4.0/I2SCK1)
CAN1_TX: IC1.1 (TXD), U$14.27 (PB14/I14/SERCOM4.2/PCC8)
CAN_H: IC1.7 (CANH), R10.2, X4.3
CAN_L: IC1.6 (CANL), R11.2, X4.1
CC1: R13.2, X6.A5 (CC1)
CC2: R12.2, X6.B5 (CC2)
D4: JP1.1, U$14.31 (PA14/I14/SERCOM2+4.2)
D5: JP3.10, U$14.35 (PA16/I2C/I0/SERCOM1.0+3.1)
D6: JP3.9, U$14.37 (PA18/I2/SERCOM1+3.2)
D8_NEOPIX: LED1.1 (DI), U$14.63 (PB02/I2/AIN14/SERCOM5.0)
D9: JP3.8, U$14.38 (PA19/I3/SERCOM1+3.3)
D10: JP3.7, U$14.41 (PA20/I4/SERCOM3+5.2/I2SFS0)
D11: JP3.6, U$14.42 (PA21/I5/SERCOM3+5.3/I2SDO)
D12: JP3.5, U$14.43 (PA22/I2C/16/SERCOM3.0+5.1/I2SDI)
D13: JP3.4, R7.1, U$14.44 (PA23/I2C/I7/SERCOM3.1+5.0/SOF/I2SFS1)
D+: D+1.TP, U$14.46 (PA25/19/SERCOM3+5.3/D+), X6.A6 (D+), X6.B6 (D+)
D-: D-1.TP, U$14.45 (PA24/I8/SERCOM3+5.2/D-), X6.A7 (D-), X6.B7 (D-)
EN: JP3.2, R3.1, U2.3 (EN)
GND: C2.2, C3.2, C4.2, C5.2, C6.2, C7.2, C8.2, C10.2, C11.2, C12.1, C13.2, C14.2, C15.2, C16.2, C17.2, IC1.2 (GND), IC3.2 (GND), JP1.13, L0.C, LED1.4 (GND), R8.2, R9.3 (1), R9.7 (2), R12.1, R13.1, SW1.B (S), SW1.B' (S1), U1.4 (VSS), U2.2 (GND), U3.2 (VSS), U$14.7 (GND_0), U$14.22 (GND_1), U$14.33 (GND_2), U$14.47 (GND_3), U$14.54 (GND_4), U$14.EXP (GND_0), X1.1, X4.2, X6.A1B12 (GND), X6.B1A12 (GND)
MISO: JP1.4, U$14.49 (PB22/I6/SERCOM1+5.2)
MOSI: JP1.5, U$14.50 (PB23/I7/SERCOM1+5.3)
unnamed: CHG0.C, R2.1
unnamed: L0.A, R7.2
unnamed: R2.2, U3.1 (STAT)
unnamed: R8.1, U3.5 (PROG)
unnamed: R10.1, SJ2.2
unnamed: C4.1, U$14.1 (PA00/EINT0/SERCOM1.0), X2.P$2
unnamed: C18.2, IC3.6 (C+)
unnamed: C18.1, IC3.4 (C-)
unnamed: C2.1, U$14.2 (PA01/EINT1/SERCOM1.1), X2.P$1
unnamed: L2.P$2 (2), U$14.55 (VSW)
unnamed: R11.1, SJ2.1
NEO_PWR: LED1.2 (VDD), U$14.64 (PB03/I3/AIN15/SERCOM5.1)
QSPI_CS: R5.1, U1.1 (SSEL), U$14.24 (PB11/I11/SERCOM4.3/I2SFS1)
QSPI_DATA[0]: U1.5 (MOSI), U$14.17 (PA08/I2C/AIN8/SERCOM0.0+2.1/I2SMCK)
QSPI_DATA[1]: U1.2 (MISO), U$14.18 (PA09/I2C/I9/AIN9/SERCOM0.1+2.0/I2SFS0)
QSPI_DATA[2]: U1.3 (WP#/IO2), U$14.19 (PA10/I10/AIN10/SERCOM0+2.2/I2SCK)
QSPI_DATA[3]: U1.7 (HOLD#/IO3), U$14.20 (PA11/I11/AIN11/SERCOM0+2.3/I2SDO)
QSPI_SCK: U1.6 (SCK), U$14.23 (PB10/I10/SERCOM4.2/I2SDI)
RX_D0: JP1.3, U$14.40 (PB17/SERCOM5.1/I2SMCK0)
SCK: JP1.6, U$14.36 (PA17/I2C/I1/SERCOM1.1+3.0)
SCL: JP3.11, U$14.30 (PA13/I13/I2C/SERCOM2.1+4.0)
SDA: JP3.12, U$14.29 (PA12/I12/I2C/SERCOM2.0+4.1)
SWCLK: R6.2, TP1.P$1, U$14.57 (PA30/I14/SERCOM1.2/SWCLK)
SWDIO: TP2.P$1, U$14.58 (PA31/I15/SERCOM1.3/SWDIO)
TX_D1: JP1.2, U$14.39 (PB16/I0/SERCOM5.0/I2SCK0)
VBAT: C3.1, JP3.1, Q3.3 (D), R9.8 (2), U3.3 (VBAT), X1.2
VBUS: CHG0.A, D4.A, JP3.3, Q3.1 (G), R9.6 (2), U3.4 (VDD), X6.A4B9 (VBUS), X6.B4A9 (VBUS)
VDDCORE1: C13.1, C15.1, L2.P$1 (1), U$14.53 (VDDCORE)
VHI: C6.1, C17.1, D4.C, IC3.5 (VIN), Q3.2 (S), R3.2, U2.1 (IN)
V_DIV: R9.1, R9.2 (1), U$14.61 (PB00/I0/AIN12/SERCOM5.2)
~RESET: C12.2, JP1.16, R4.2, SW1.A, SW1.A' (P1), U$14.52 (~RESET)

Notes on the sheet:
PCCD2
RESET
PCCD7
USB AND BATTERY CHARGING
PCCD1
PCCD4
Internal SPI on SERCOM 2
CAN0_TX
PCCDEN2
10K = 100mA
PCCD3
RED LED
PCCD5
5.0K = 200mA
PCCD0
PCC: DEN1: SDA DEN2: SCL CLK: D6 D0: D11 D1: D13 D2: D10 D3: D12 D4: MISO D5: D5 D6: MOSI D7: SCK SPI: SERCOM1 DOPO = 0x3, SCK.1 & MO.3, MI.2 I2C: SERCOM2 or 4 UART: SERCOM5, TX on .0 & RX on .1 SPI Flash: QSPI (dual io) I2S: SCK0: A2 FS0: MISO SDI: MOSI SDO: D5 TCC1: WO0: D11 WO1: D13 WO2: D10 WO3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
PCCD6
DAC1
BREAKOUTS
2.0K = 500mA
PCCDEN1
CAN0_RX
POWER AND FILTERING
PCCLK
DAC0
1.0K = 1000mA

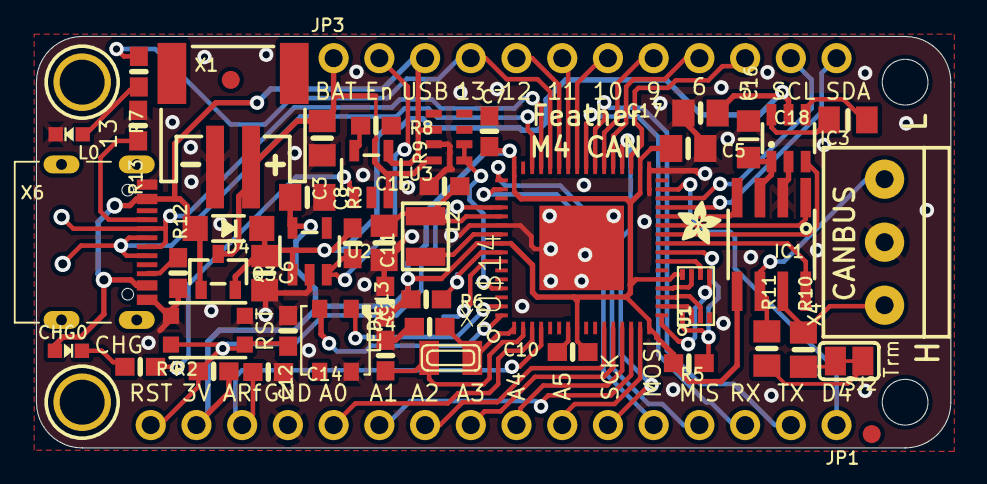
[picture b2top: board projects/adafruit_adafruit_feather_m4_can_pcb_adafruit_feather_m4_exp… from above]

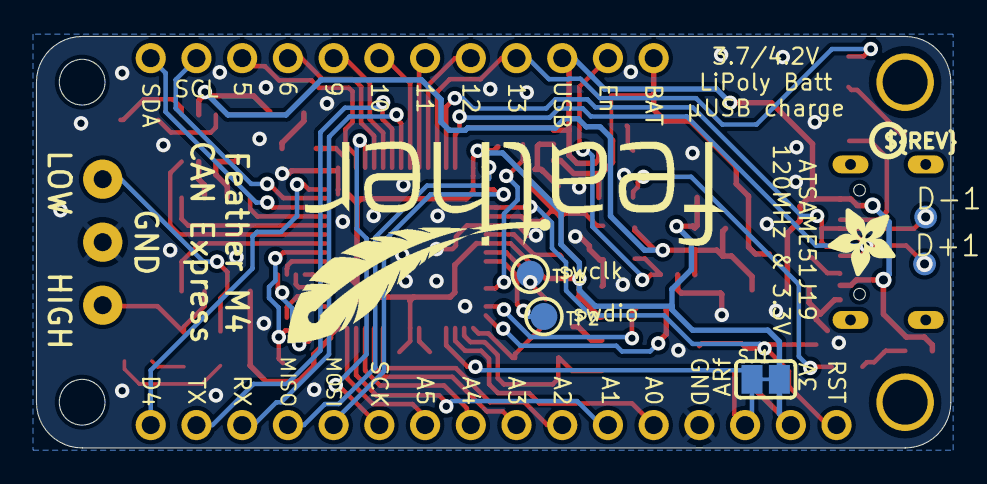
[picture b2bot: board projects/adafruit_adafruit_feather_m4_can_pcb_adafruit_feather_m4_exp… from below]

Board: 2 copper layers, 50.8 x 22.9 mm, 63 parts (8 on the bottom side), 63 nets.

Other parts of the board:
@HOLE0, @HOLE1: (no value)
U$1: ADAFRUIT_2.5MM
U$9: FEATHERLOGO
U$12: ADAFRUIT_3.5MM
U$13: PCBFEAT-REV-040

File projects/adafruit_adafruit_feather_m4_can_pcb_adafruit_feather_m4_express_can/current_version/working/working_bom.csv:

"Id";"Designator";"Footprint";"Quantity";"Designation";"Supplier and ref";
1;"C11,C12,C15,C14,C10,C7";"0603-NO";6;"1uF";;;
2;"X6";"USB_C_CUSB31-CFM2AX-01-X";1;"USB Type C";;;
3;"C13,C17,C5";"0805-NO";3;"10uF";;;
4;"R12,R13,R8";"0603-NO";3;"5.1K";;;
5;"X1";"JSTPH2_BATT";1;"JSTPH";;;
6;"U$35,U$34";"FIDUCIAL_1MM";2;"FIDUCIAL_1MM";;;
7;"U3";"SOT23-5";1;"MCP73831T-2ACI/OT";;;
8;"R9";"RESPACK_4X0603_NO";1;"100K";;;
9;"C6,C8,C3";"0805-NO";3;"10µF";;;
10;"R2,R7,R5,R4,R6,R3";"0603-NO";6;"10K";;;
11;"X2";"XTAL3215";1;"32.768";;;
12;"U$32,U$31";"MOUNTINGHOLE_2.5_PLATED";2;"MOUNTINGHOLE2.5";;;
13;"SW1";"BTN_KMR2_4.6X2.8";1;"KMR2";;;
14;"JP1";"1X16_ROUND";1;"";;;
15;"U$1";"ADAFRUIT_2.5MM";1;"";;;
16;"@HOLE0,@HOLE1";"";2;"";;;
17;"CHG0";"CHIPLED_0603_NOOUTLINE";1;"ORANGE";;;
18;"C2,C4";"0603-NO";2;"22pF";;;
19;"SJ2,SJ1";"SOLDERJUMPER_CLOSEDWIRE";2;"";;;
20;"U$14";"PQFN64-1";1;"ATSAMD51J";;;
21;"JP3";"1X12_ROUND";1;"";;;
22;"C16";"_0805MP";1;"10uF";;;
23;"U1";"USON8";1;"2MB Flash";;;
24;"L0";"CHIPLED_0603_NOOUTLINE";1;"RED";;;
25;"R11,R10";"0805-NO";2;"60 ohm";;;
26;"IC3";"SOT23-6";1;"AP3602";;;
27;"Q3";"SOT23-R";1;"DMG341";;;
28;"LED1";"LED3535";1;"WS2812B3535";;;
29;"X4";"TERMBLOCK_1X3-3.5MM";1;"3.5mm";;;
30;"U2";"SOT23-5@1";1;"AP2112-3.3";;;
31;"IC1";"SOIC8_150MIL";1;"TCAN1051HGV";;;
32;"D4";"SOD-123";1;"MBR540";;;
33;"L2";"INDUCTOR_1007";1;"10uH";;;
34;"C18";"0805_10MGAP";1;"1uF";;;
35;"D-1,D+1";"B1,27";2;"TPB1,27";;;
36;"U$12";"ADAFRUIT_3.5MM";1;"";;;
37;"U$9";"FEATHERLOGO";1;"";;;
38;"TP2,TP1";"TESTPOINT_ROUND_1.5MM";2;"";;;
39;"U$13";"PCBFEAT-REV-040";1;"";;;
